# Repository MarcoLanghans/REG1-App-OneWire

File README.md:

Onewire Extension Card for OpenKNX REG1 BASE Device https://openknx.atlassian.net/wiki/spaces/OpenKNX/pages/7667822/OpenKNX+REG1+Basismodul (But you need the Case of the Universal Extension Version)
<br>
The Extension Card is no official created OpenKNX Hardware, so the usage is your personal risk. 
<br>
But it runs now since several days inside my person lab without any issues.

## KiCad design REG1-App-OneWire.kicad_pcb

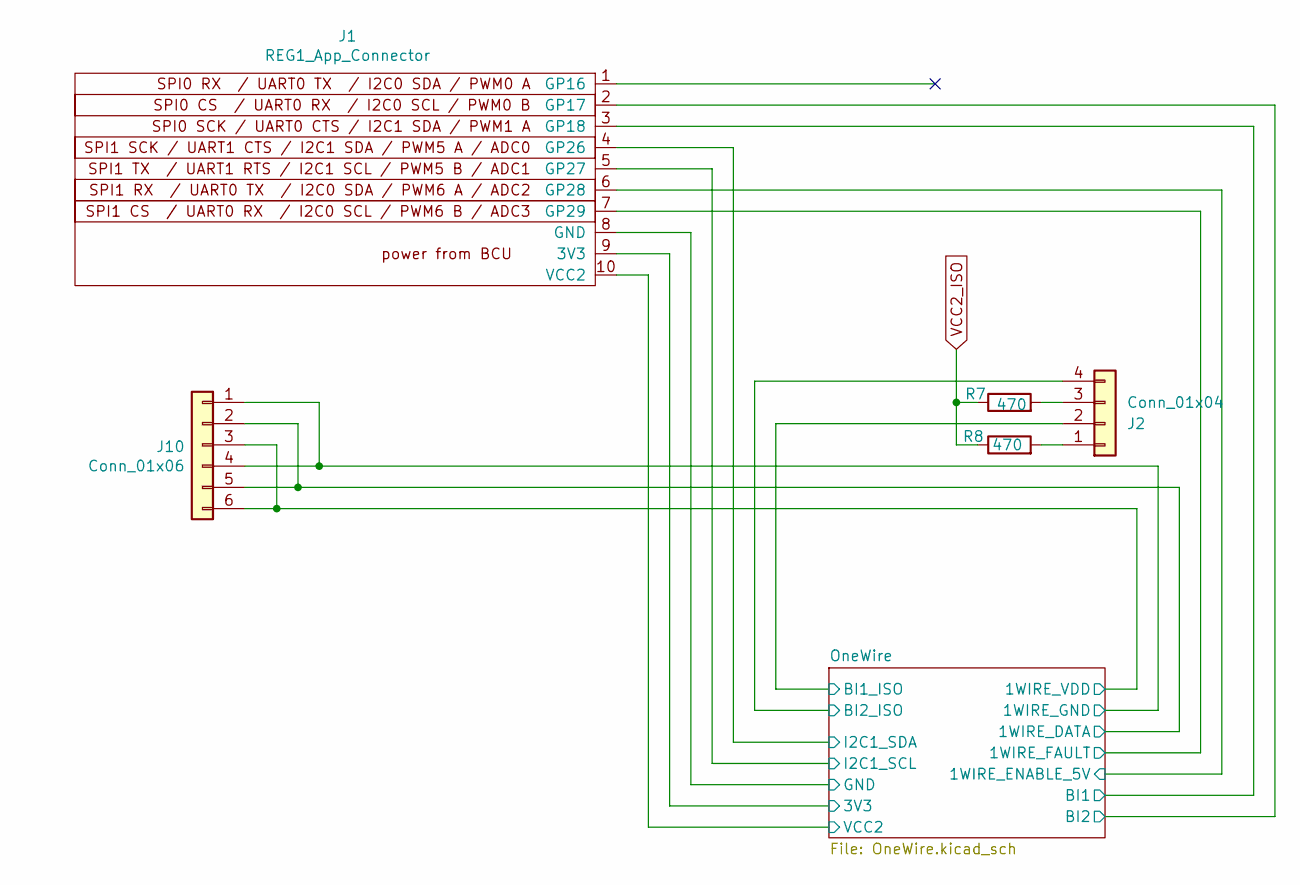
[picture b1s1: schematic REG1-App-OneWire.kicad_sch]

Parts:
J1: REG1_App_Connector; PinHeader_1x10_P2.54mm_Horizontal; LCSC C706873
J2: Conn_01x04; PhoenixContact_MC_1,5_4-G-3.5_1x04_P3.50mm_Horizontal
J10: Conn_01x06; PhoenixContact_MC_1,5_6-G-3.5_1x06_P3.50mm_Horizontal; LCSC C441175
R7, R8: 470; R_0603_1608Metric; MPN C23179

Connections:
/OneWire/1WIRE_DATA: J10.2, J10.5; also elsewhere on the board
/OneWire/1WIRE_ENABLE_5V: J1.6 (GP28); also elsewhere on the board
/OneWire/1WIRE_FAULT: J1.7 (GP29); also elsewhere on the board
/OneWire/1WIRE_GND: J10.1, J10.4; also elsewhere on the board
/OneWire/1WIRE_VDD: J10.3, J10.6; also elsewhere on the board
/OneWire/3V3: J1.9 (3V3); also elsewhere on the board
/OneWire/BI1: J1.3 (GP18); also elsewhere on the board
/OneWire/BI1_ISO: J2.2; also elsewhere on the board
/OneWire/BI2: J1.2 (GP17); also elsewhere on the board
/OneWire/BI2_ISO: J2.4; also elsewhere on the board
/OneWire/GND: J1.8 (GND); also elsewhere on the board
/OneWire/I2C1_SCL: J1.5 (GP27); also elsewhere on the board
/OneWire/I2C1_SDA: J1.4 (GP26); also elsewhere on the board
/OneWire/VCC2: J1.10 (VCC2); also elsewhere on the board
unnamed: J2.1, R8.2
unnamed: J2.3, R7.2
VCC2_ISO: R7.1, R8.1; also elsewhere on the board

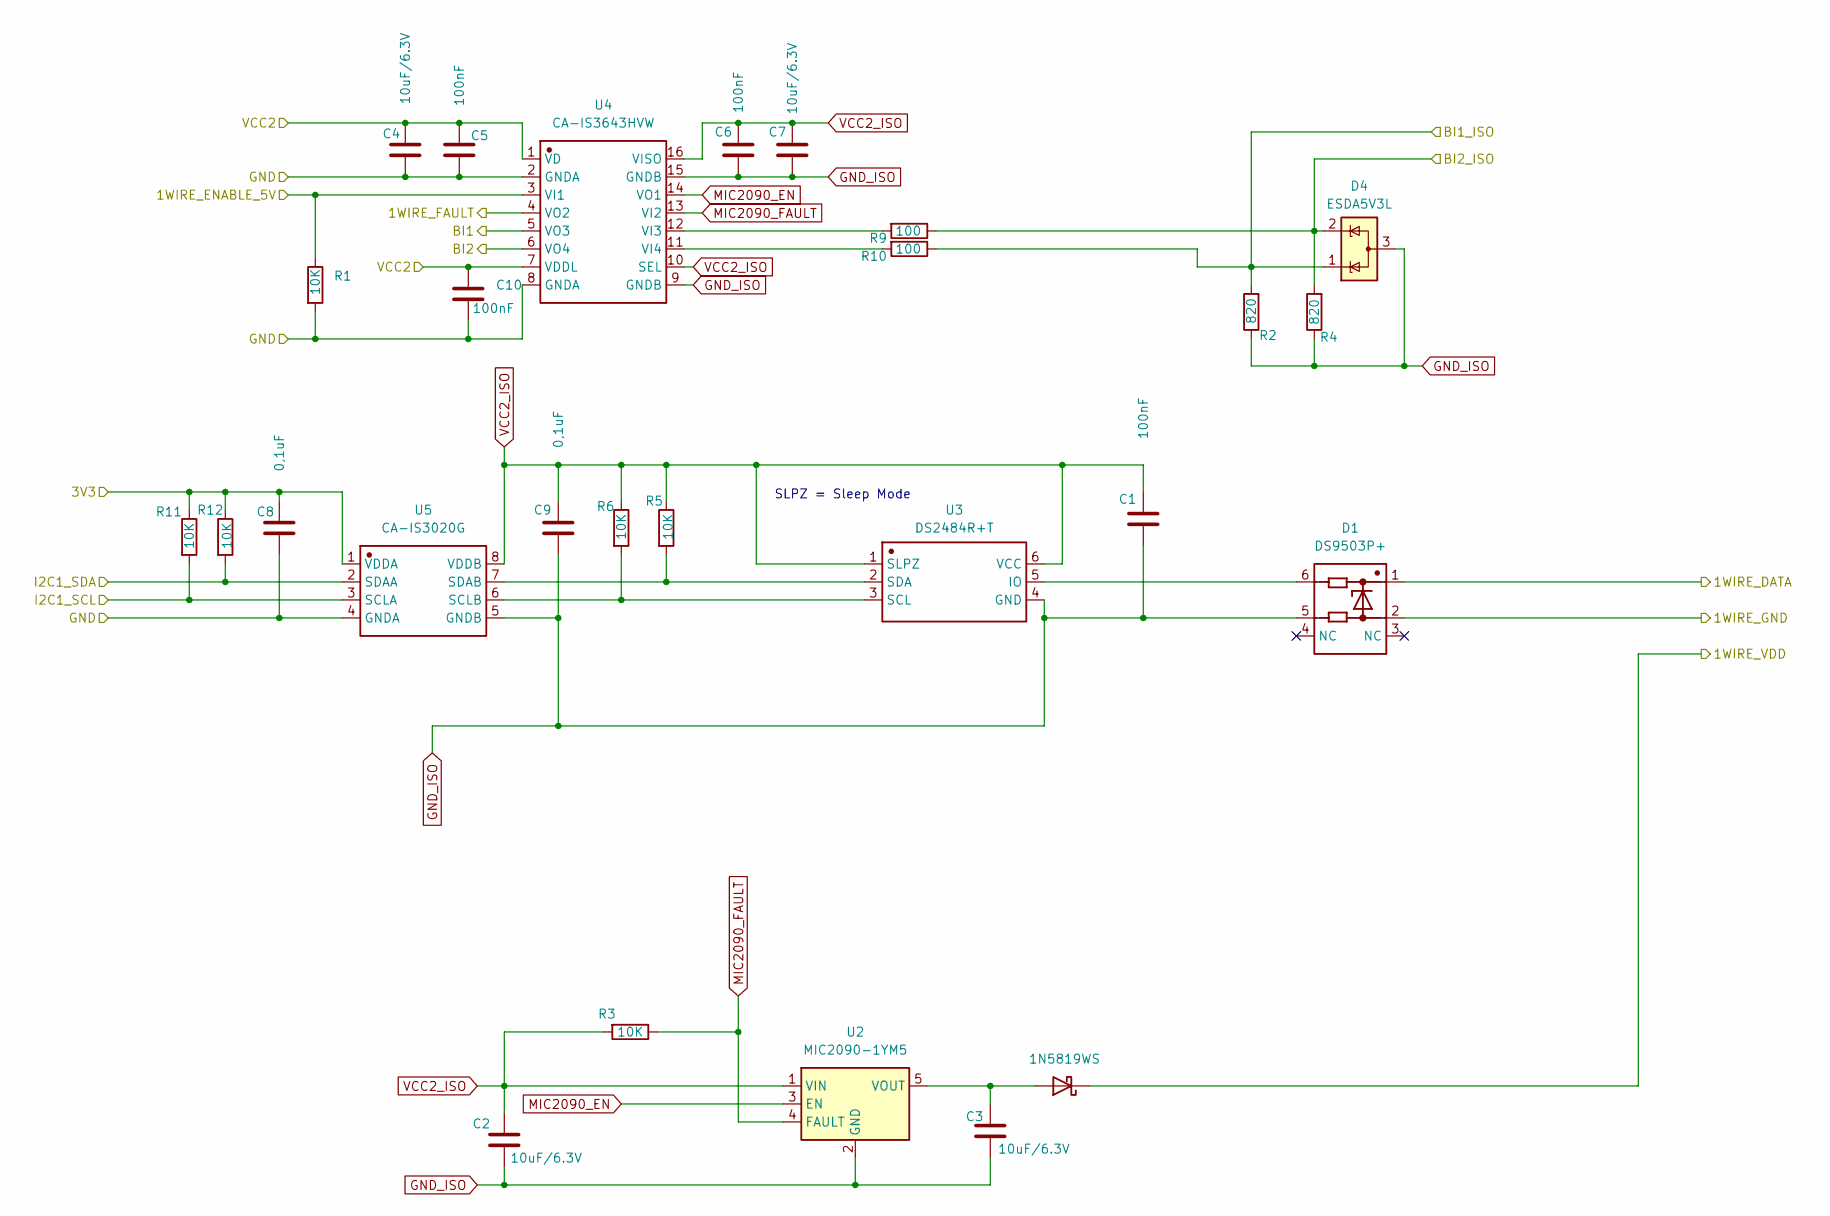
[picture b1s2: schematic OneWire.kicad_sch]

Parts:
C1, C5, C6, C10: 100nF; C_0402_1005Metric
C2, C3, C4, C7: 10uF/6.3V; C_0402_1005Metric; MPN C15525
C8, C9: 0,1uF; C_0402_1005Metric
D1: DS9503P+; Manufacturer Part DS9503P+
D2: 1N5819WS; D_SOD-323; MPN C191023
D4: ESDA5V3L; SOT-23-3; MPN C502554
R1, R3, R5, R6, R11, R12: 10K; R_0603_1608Metric; MPN C25804
R2, R4: 820; R_0603_1608Metric; MPN C23253
R9, R10: 100; R_0603_1608Metric; MPN C22775
U2: MIC2090-1YM5; SOT-23-5
U3: DS2484R+T; Manufacturer Part DS2484R+T
U4: CA-IS3643HVW; CA-IS3643HVW (C7422549); Manufacturer Part CA-IS3643HVW
U5: CA-IS3020G; CA-IS3020G (C5156914); Manufacturer Part CA-IS3020G

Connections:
/OneWire/1WIRE_DATA: D1.1; also elsewhere on the board
/OneWire/1WIRE_ENABLE_5V: R1.1, U4.3 (VI1); also elsewhere on the board
/OneWire/1WIRE_FAULT: U4.4 (VO2); also elsewhere on the board
/OneWire/1WIRE_GND: D1.2; also elsewhere on the board
/OneWire/1WIRE_VDD: D2.1 (K); also elsewhere on the board
/OneWire/3V3: C8.1, R11.1, R12.1, U5.1 (VDDA); also elsewhere on the board
/OneWire/BI1: U4.5 (VO3); also elsewhere on the board
/OneWire/BI1_ISO: D4.1 (K), R2.2, R10.1; also elsewhere on the board
/OneWire/BI2: U4.6 (VO4); also elsewhere on the board
/OneWire/BI2_ISO: D4.2 (K), R4.2, R9.1; also elsewhere on the board
/OneWire/GND: C4.2, C5.2, C8.2, C10.2, R1.2, U4.2 (GNDA), U4.8 (GNDA), U5.4 (GNDA); also elsewhere on the board
/OneWire/I2C1_SCL: R11.2, U5.3 (SCLA); also elsewhere on the board
/OneWire/I2C1_SDA: R12.2, U5.2 (SDAA); also elsewhere on the board
/OneWire/VCC2: C4.1, C5.1, C10.1, U4.1 (VD), U4.7 (VDDL); also elsewhere on the board
GND_ISO: C1.1, C2.2, C3.2, C6.1, C7.1, C9.2, D1.5, D4.3 (A), R2.1, R4.1, U2.2 (GND), U3.4 (GND), U4.9 (GNDB), U4.15 (GNDB), U5.5 (GNDB)
MIC2090_EN: U2.3 (EN), U4.14 (VO1)
MIC2090_FAULT: R3.1, U2.4 (FAULT), U4.13 (VI2)
unnamed: D1.6, U3.5 (IO)
unnamed: C3.1, D2.2 (A), U2.5 (VOUT)
unnamed: R6.2, U3.3 (SCL), U5.6 (SCLB)
unnamed: R5.2, U3.2 (SDA), U5.7 (SDAB)
unnamed: R9.2, U4.12 (VI3)
unnamed: R10.2, U4.11 (VI4)
VCC2_ISO: C1.2, C2.1, C6.2, C7.2, C9.1, R3.2, R5.1, R6.1, U2.1 (VIN), U3.1 (SLPZ), U3.6 (VCC), U4.10 (SEL), U4.16 (VISO), U5.8 (VDDB); also elsewhere on the board

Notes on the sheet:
SLPZ = Sleep Mode

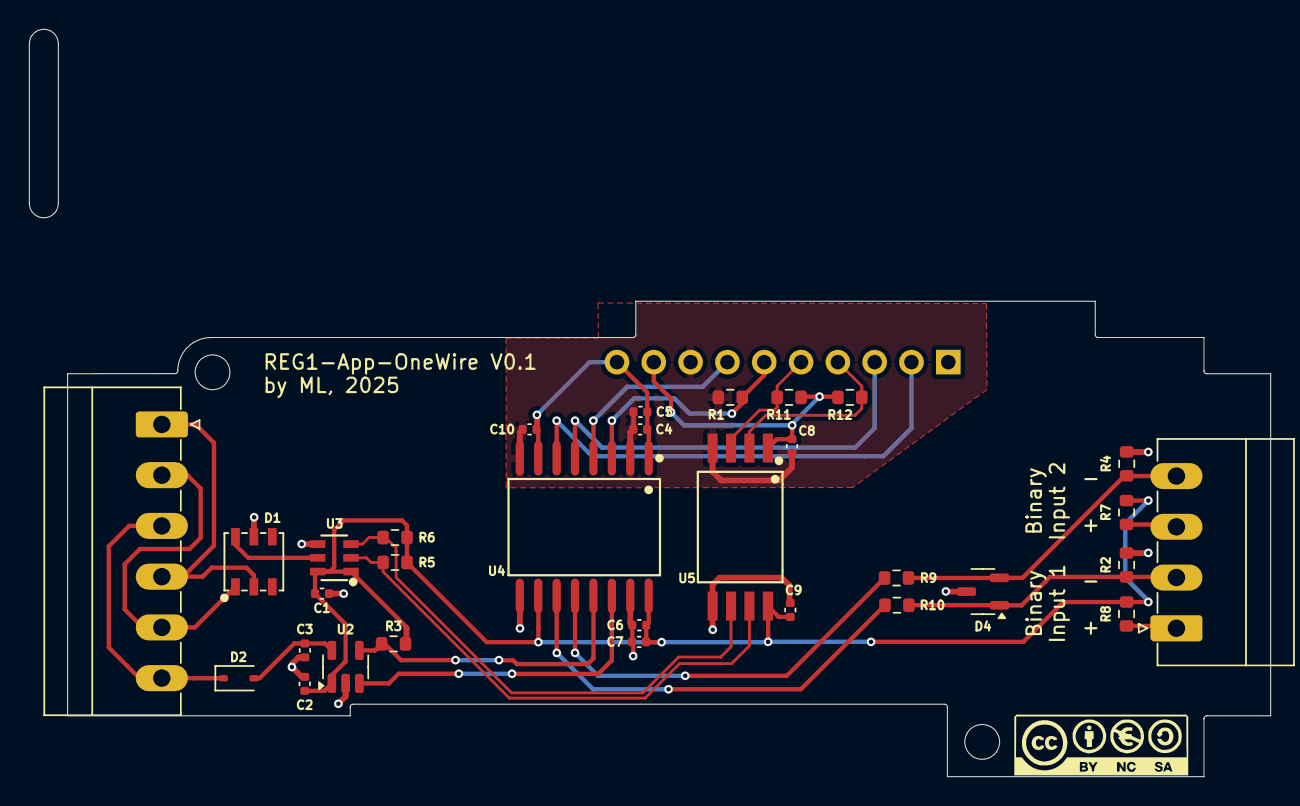
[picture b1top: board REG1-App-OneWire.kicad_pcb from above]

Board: 2 copper layers, 85.6 x 51.6 mm, 33 parts (1 on the bottom side), 26 nets.

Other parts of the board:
G*: LOGO; CC-BY-NY-SA_12x4

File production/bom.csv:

Designator,Footprint,Quantity,Value,LCSC Part #
"C1, C10, C5, C6",0402,4,100nF,
"C2, C3, C4, C7",0402,4,10uF/6.3V,C15525
"C8, C9",0402,2,"0,1uF",
D1,DS9503P+,1,DS9503P+,C879660
D2,D_SOD-323,1,1N5819WS,C191023
D4,SOT-23-3,1,ESDA5V3L,C502554
J1,PinHeader_1x10_P2.54mm_Horizontal,1,REG1_App_Connector,C706873
"R1, R11, R12, R3, R5, R6",0603,6,10K,C25804
"R10, R9",0603,2,100,C22775
"R2, R4",0603,2,820,C23253
"R7, R8",0603,2,470,C23179
U2,SOT-23-5,1,MIC2090-1YM5,C625685
U3,DS2484R+T,1,DS2484R+T,C124886
U4,CA-IS3643HVW (C7422549),1,CA-IS3643HVW,
U5,CA-IS3020G (C5156914),1,CA-IS3020G,

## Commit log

2026-01-06 Add files via upload
    Not Production, only for development
